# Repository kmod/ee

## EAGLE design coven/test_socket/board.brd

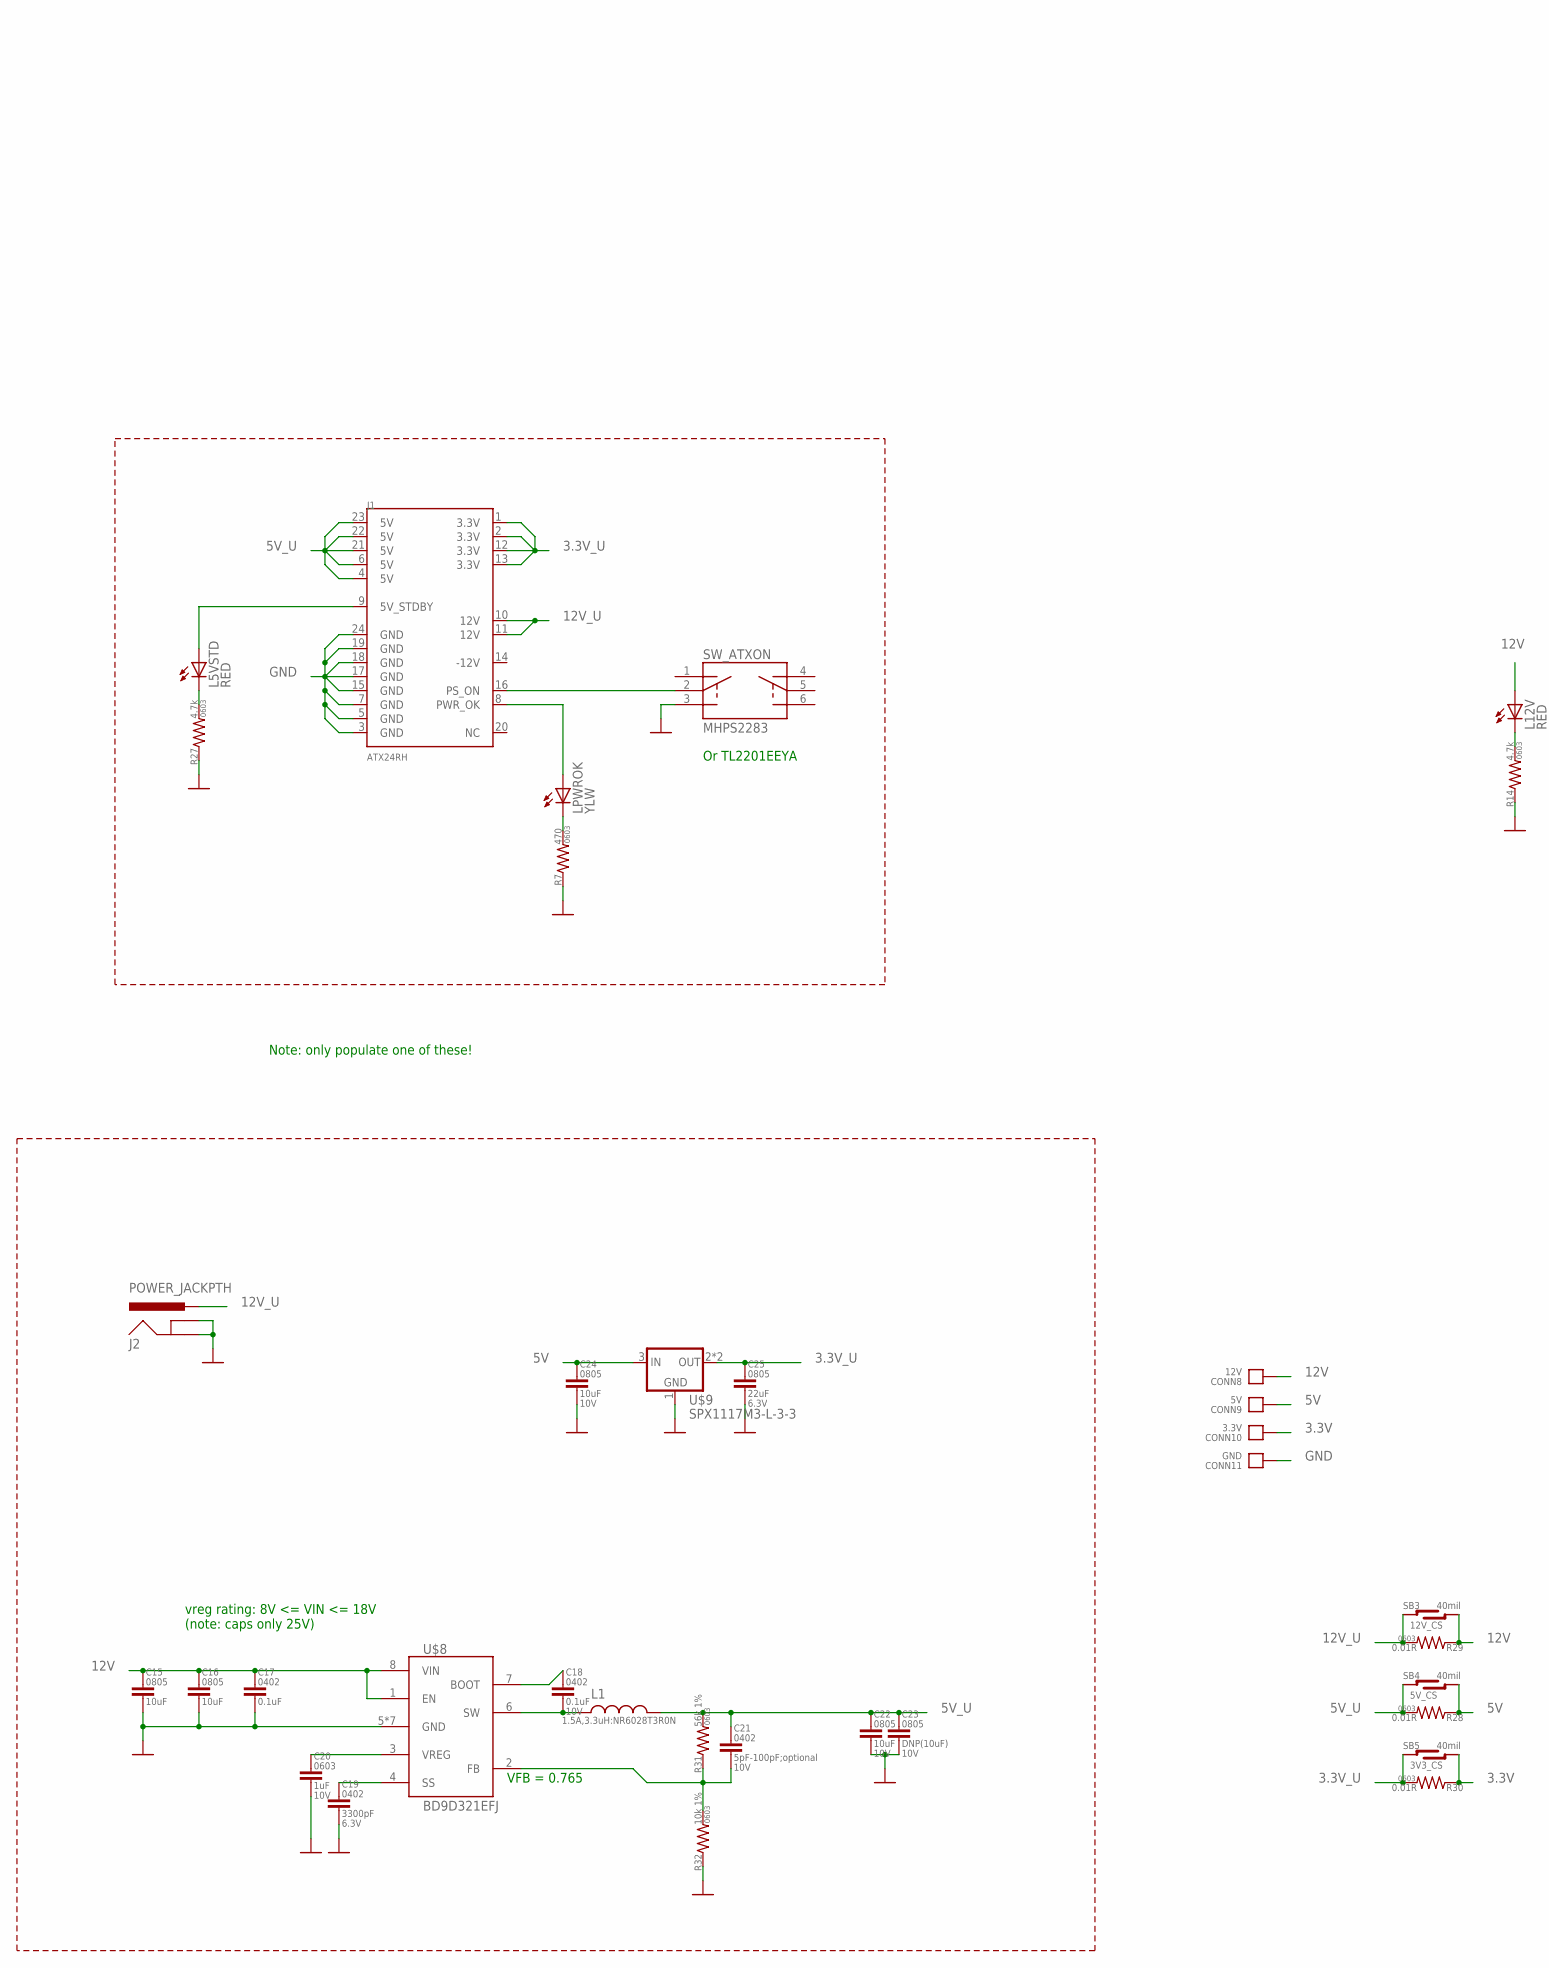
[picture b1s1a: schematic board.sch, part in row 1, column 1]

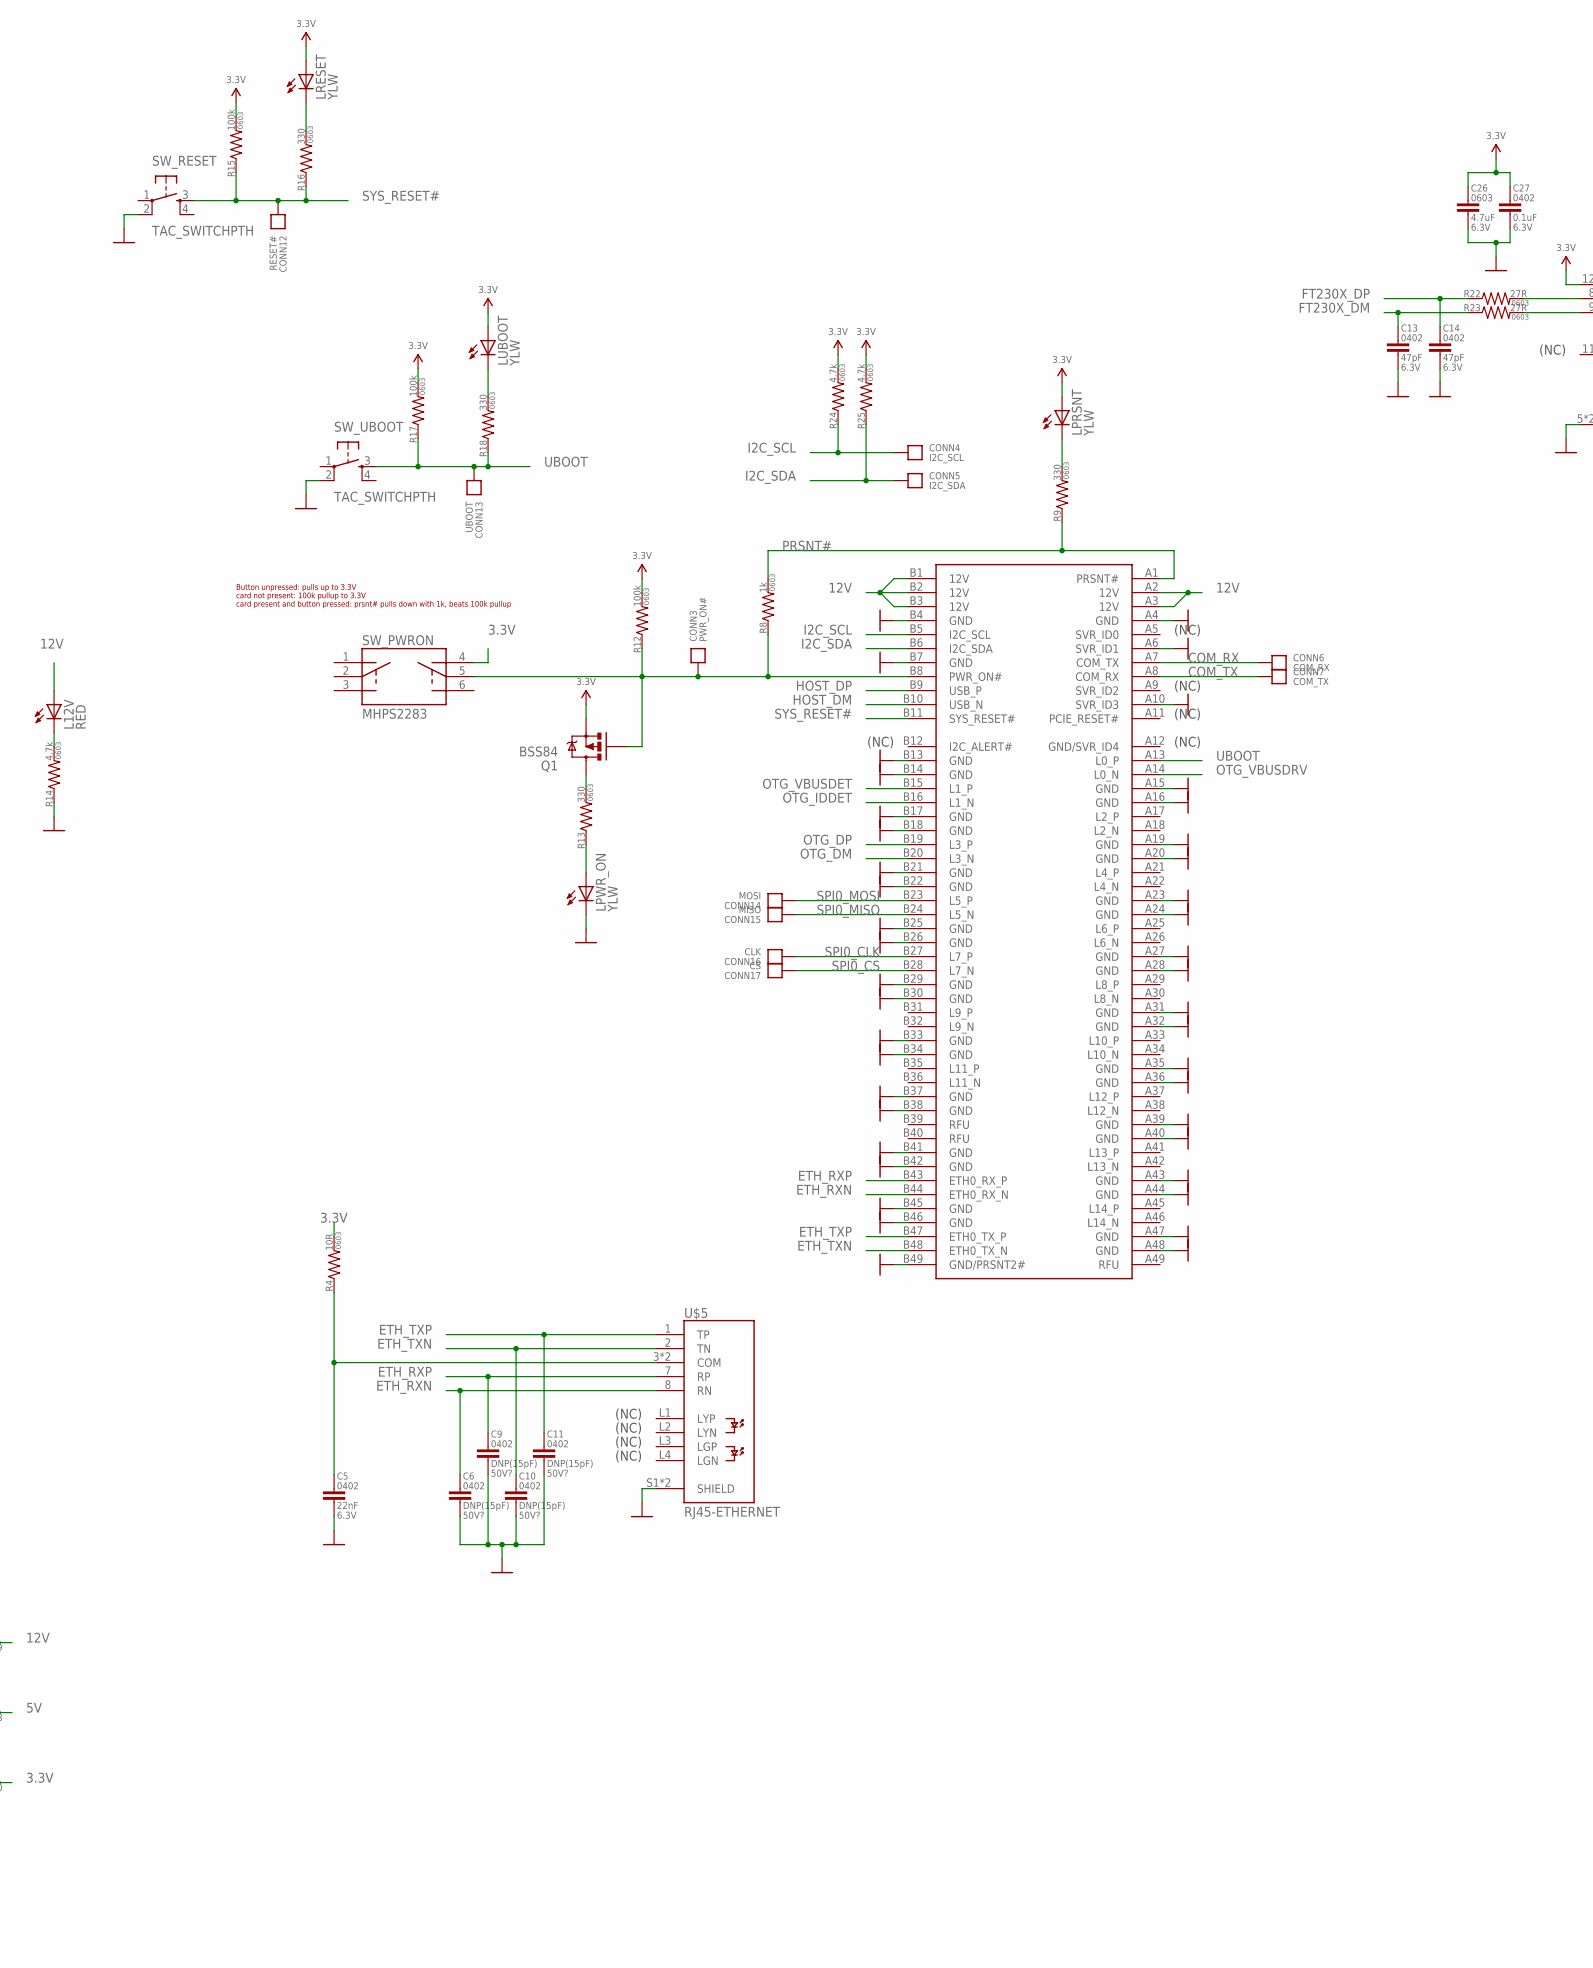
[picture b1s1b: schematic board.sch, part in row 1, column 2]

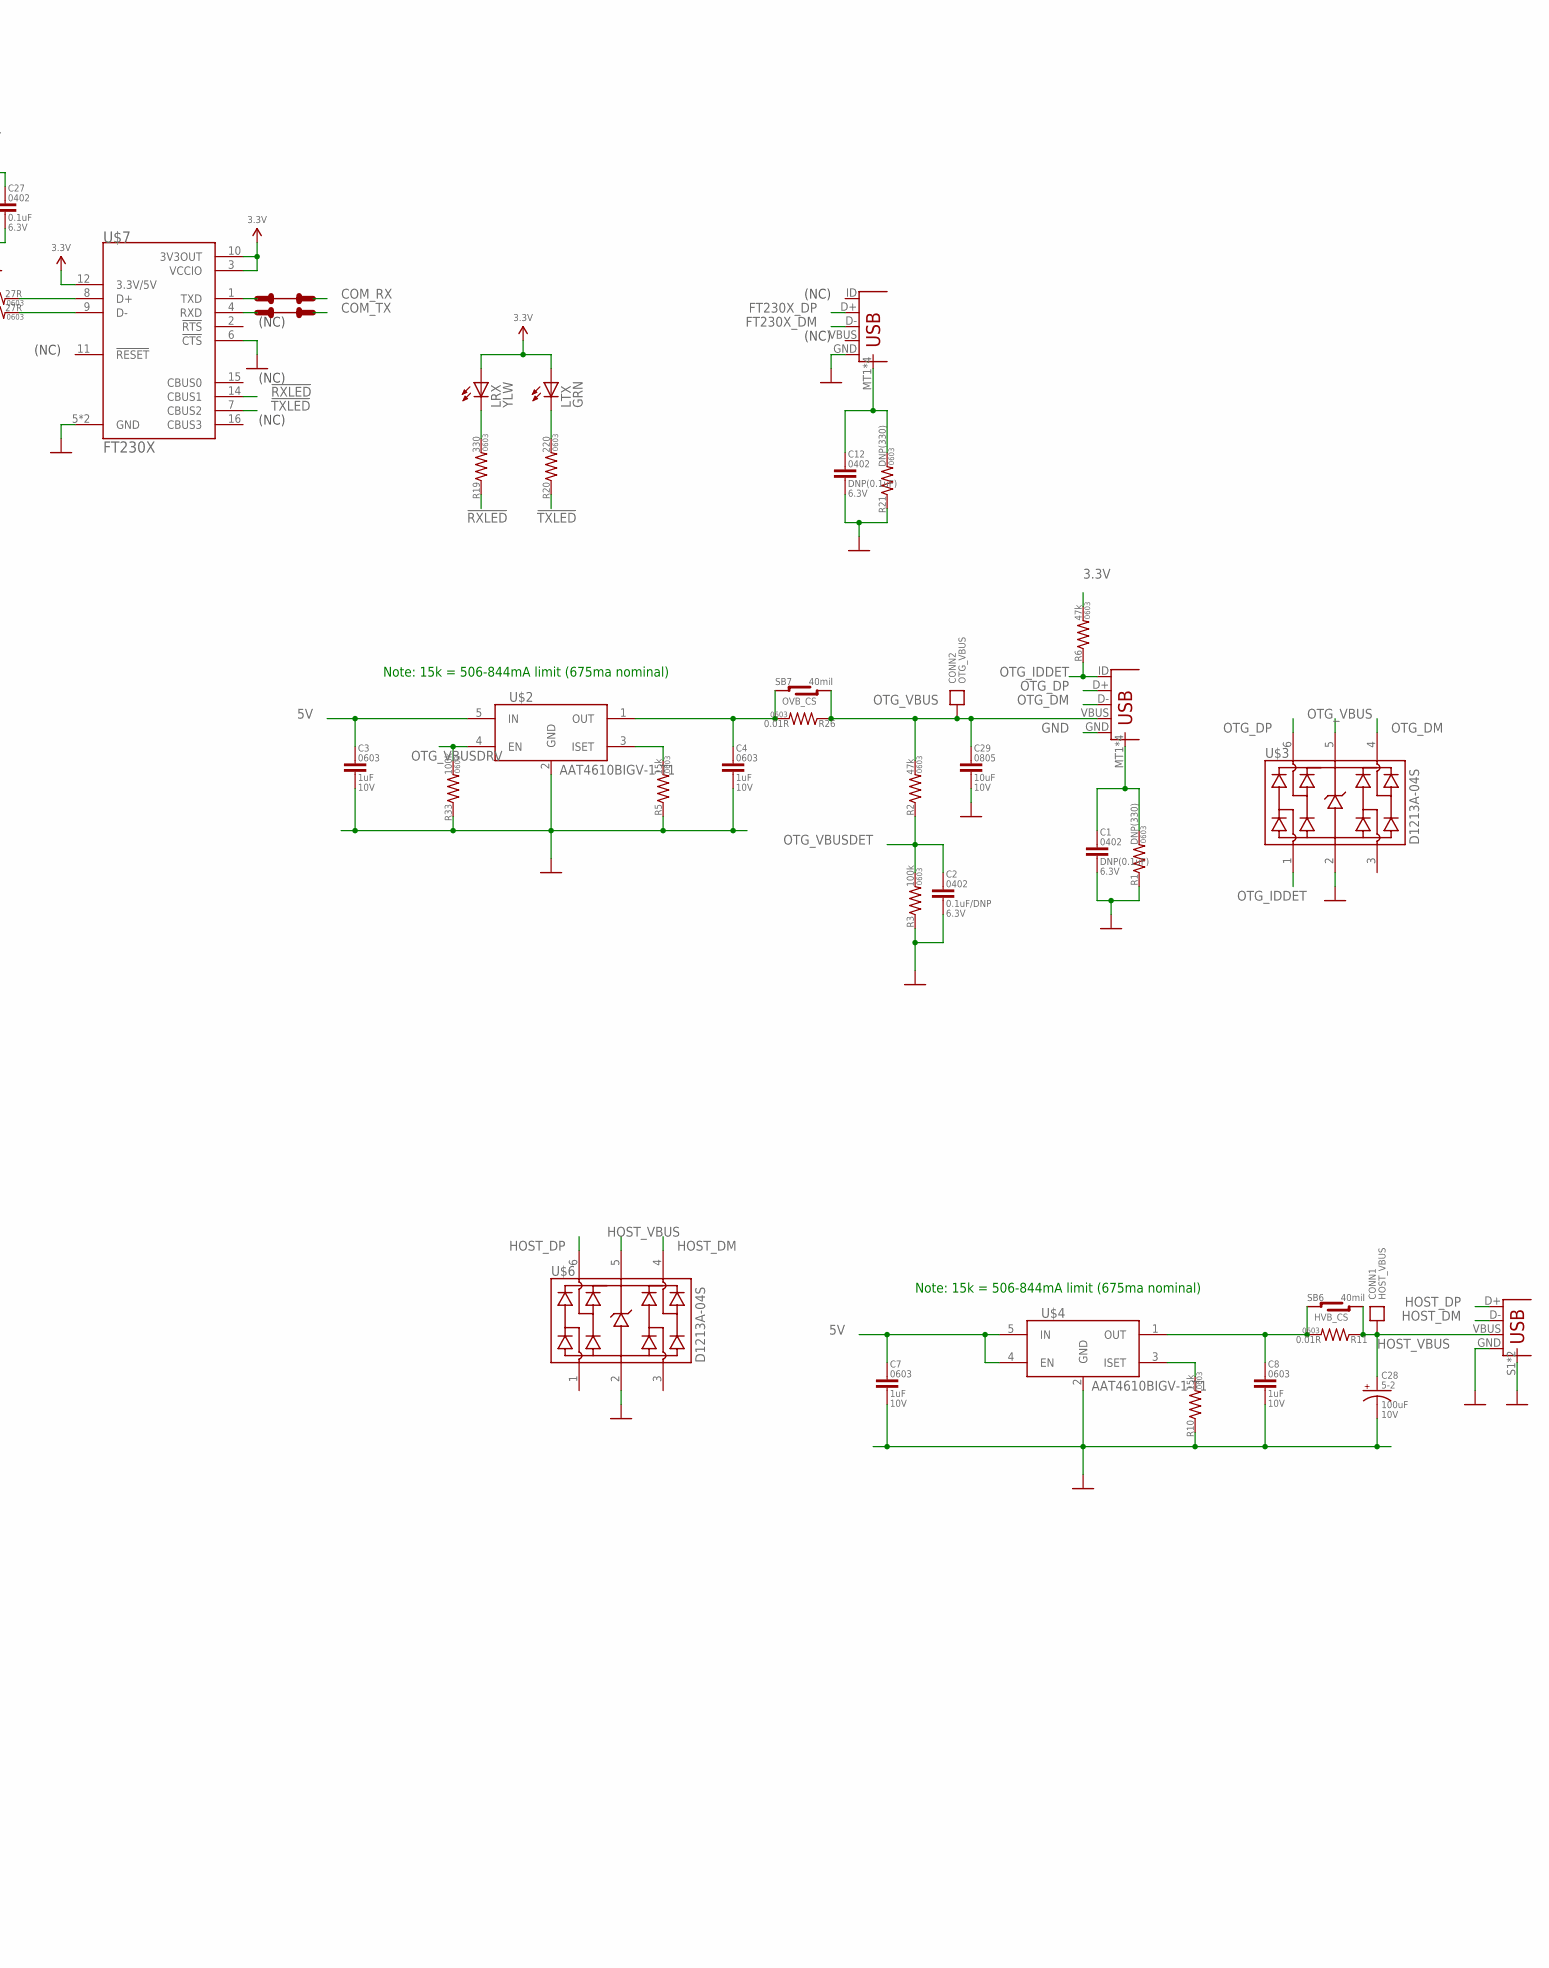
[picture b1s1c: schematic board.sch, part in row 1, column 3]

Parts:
C1, C12: DNP(0.1uF); 0402-CAP
C2: 0.1uF/DNP; 0402-CAP
C3, C4, C7, C8, C20: 1uF; 0603-CAP; VOLTAGE 10V
C5: 22nF; 0402-CAP
C6, C9, C10, C11: DNP(15pF); 0402-CAP; VOLTAGE 50V?
C13, C14: 47pF; 0402-CAP
C15, C16: 10uF; 0805; VOLTAGE 25V
C17: 0.1uF; 0402-CAP; VOLTAGE 25V
C18: 0.1uF; 0402-CAP; VOLTAGE 10V
C19: 3300pF; 0402-CAP
C21: 5pF-100pF;optional; 0402-CAP; VOLTAGE 10V
C22, C24, C29: 10uF; 0805; VOLTAGE 10V
C23: DNP(10uF); 0805; VOLTAGE 10V
C25: 22uF; 0805
C26: 4.7uF; 0603-CAP
C27: 0.1uF; 0402-CAP
C28: 100uF; CAP-5-2; VOLTAGE 10V
CONN1: HOST_VBUS; HOLE_22AWG
CONN2: OTG_VBUS; HOLE_22AWG
CONN3: PWR_ON#; HOLE_22AWG
CONN4: I2C_SCL; HOLE_22AWG
CONN5: I2C_SDA; HOLE_22AWG
CONN6: COM_RX; HOLE_22AWG
CONN7: COM_TX; HOLE_22AWG
CONN8: 12V; HOLE_22AWG
CONN9: 5V; HOLE_22AWG
CONN10: 3.3V; HOLE_22AWG
CONN11: GND; HOLE_22AWG
CONN12: RESET#; HOLE_22AWG
CONN13: UBOOT; HOLE_22AWG
CONN14: MOSI; HOLE_22AWG
CONN15: MISO; HOLE_22AWG
CONN16: CLK; HOLE_22AWG
CONN17: CS; HOLE_22AWG
J1: ATX24RH; ATX24_RIGHT_ANGLE
J2: POWER_JACKPTH; POWER_JACK_PTH
JP1, JP2: USB-IDMICRO; USB-MICRO
JP3: USBA-FEMALE-TH; USB-A-SOCKET-TH
L1: 1.5A,3.3uH:NR6028T3R0N; NR60XX
L5VSTD, L12V: RED; 0603_LED
LPRSNT: YLW; 0603_LED
LPWROK: YLW; 0603_LED
LPWR_ON: YLW; 0603_LED
LRESET: YLW; 0603_LED
LRX: YLW; 0603_LED
LTX: GRN; 0603_LED
LUBOOT: YLW; 0603_LED
Q1: BSS84; SOT23-3
R1, R21: DNP(330); 0603-RES
R2, R6: 47k; 0603-RES
R3, R12, R15, R17, R33: 100k; 0603-RES
R4: 10R; 0603-RES
R5, R10: 15k; 0603-RES
R7: 470; 0603-RES
R8: 1k; 0603-RES
R9, R13, R16, R18, R19: 330; 0603-RES
R11, R26, R28, R29, R30: 0.01R; 0603-RES
R14, R24, R25, R27: 4.7k; 0603-RES
R20: 220; 0603-RES
R22, R23: 27R; 0603-RES
R31: 56k 1%; 0603-RES
R32: 10k 1%; 0603-RES
SB1: RX; TRACE-CUT
SB2: TX; TRACE-CUT
SB3: 12V_CS; SOLDER-BRIDGE-OPEN-LARGE
SB4: 5V_CS; SOLDER-BRIDGE-OPEN-LARGE
SB5: 3V3_CS; SOLDER-BRIDGE-OPEN-LARGE
SB6: HVB_CS; SOLDER-BRIDGE-OPEN-LARGE
SB7: OVB_CS; SOLDER-BRIDGE-OPEN-LARGE
SW_ATXON: MHPS2283; PUSHBUTTON-2.5-5.4
SW_PWRON: MHPS2283; PUSHBUTTON-2.5-5.4
SW_RESET: TAC_SWITCHPTH; TACTILE-PTH
SW_UBOOT: TAC_SWITCHPTH; TACTILE-PTH
U$1: CVN-V1CONN; CVN-V1-CONN
U$2, U$4: AAT4610BIGV-1-T1; SOT23-5
U$3, U$6: D1213A-04S; SOT363
U$5: RJ45-ETHERNET; RJ45
U$7: FT230X; TSSOP16
U$8: BD9D321EFJ; HTSOP8
U$9: SPX1117M3-L-3-3; SOT223

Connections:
3.3V: C26.1, C27.1, CONN10.P, LPRSNT.A, LRESET.A, LRX.A, LTX.A, LUBOOT.A, Q1.2 (S), R4.2, R6.2, R12.2, R15.2, R17.2, R24.2, R25.2, R30.1, SB5.R1, SB5.R2, SW_PWRON.4 (NC1), U$7.3 (VCCIO), U$7.10 (3V3OUT), U$7.12 (3.3V/5V)
3.3V_U: C25.1, J1.1 (3.3V), J1.2 (3.3V), J1.12 (3.3V), J1.13 (3.3V), R30.2, SB5.L1, SB5.L2, U$9.2 (OUT), U$9.4 (OUT)
5V: C3.1, C7.1, C24.1, CONN9.P, R28.1, SB4.R1, SB4.R2, U$2.5 (IN), U$4.4 (EN), U$4.5 (IN), U$9.3 (IN)
5V_U: C21.1, C22.1, C23.1, J1.4 (5V), J1.6 (5V), J1.21 (5V), J1.22 (5V), J1.23 (5V), L1.P$2 (2), R28.2, R31.2, SB4.L1, SB4.L2
12V: C15.1, C16.1, C17.1, CONN8.P, L12V.A, R29.1, SB3.R1, SB3.R2, U$1.A2 (12V), U$1.A3 (12V), U$1.B1 (12V), U$1.B2 (12V), U$1.B3 (12V), U$8.1 (EN), U$8.8 (VIN)
12V_U: J1.10 (12V), J1.11 (12V), J2.PWR, R29.2, SB3.L1, SB3.L2
!RXLED: R19.1, U$7.14 (CBUS1)
!TXLED: R20.1, U$7.7 (CBUS2)
COM_RX: CONN6.P, SB1.R1, U$1.A7 (COM_TX)
COM_TX: CONN7.P, SB2.R1, U$1.A8 (COM_RX)
ETH_RXN: C6.1, U$1.B44 (ETH0_RX_N), U$5.8 (RN)
ETH_RXP: C9.1, U$1.B43 (ETH0_RX_P), U$5.7 (RP)
ETH_TXN: C10.1, U$1.B48 (ETH0_TX_N), U$5.2 (TN)
ETH_TXP: C11.1, U$1.B47 (ETH0_TX_P), U$5.1 (TP)
FT230X_DM: C13.1, JP2.D-, R23.1
FT230X_DP: C14.1, JP2.D+, R22.1
GND: C1.2, C2.2, C3.2, C4.2, C5.2, C6.2, C7.2, C8.2, C9.2, C10.2, C11.2, C12.2, C13.2, C14.2, C15.2, C16.2, C17.2, C19.2, C20.2, C22.2, C23.2, C24.2, C25.2, C26.2, C27.2, C28.2 (-), C29.2, CONN11.P, J1.3 (GND), J1.5 (GND), J1.7 (GND), J1.15 (GND), J1.17 (GND), J1.18 (GND), J1.19 (GND), J1.24 (GND), J2.GND, J2.GNDBREAK, JP1.GND, JP2.GND, JP3.GND, JP3.S1 (SHELL), JP3.S2 (SHELL), LPWR_ON.C, R1.1, R3.1, R5.1, R7.1, R10.1, R14.1, R21.1, R27.1, R32.1, R33.1, SW_ATXON.3 (NO0), SW_RESET.2, SW_UBOOT.2, U$1.A4 (GND), U$1.A6 (SVR_ID1), U$1.A10 (SVR_ID3), U$1.A15 (GND), U$1.A16 (GND), U$1.A19 (GND), U$1.A20 (GND), U$1.A23 (GND), U$1.A24 (GND), U$1.A27 (GND), U$1.A28 (GND), U$1.A31 (GND), U$1.A32 (GND), U$1.A35 (GND), U$1.A36 (GND), U$1.A39 (GND), U$1.A40 (GND), U$1.A43 (GND), U$1.A44 (GND), U$1.A47 (GND), U$1.A48 (GND), U$1.B4 (GND), U$1.B7 (GND), U$1.B13 (GND), U$1.B14 (GND), U$1.B17 (GND), U$1.B18 (GND), U$1.B21 (GND), U$1.B22 (GND), U$1.B25 (GND), U$1.B26 (GND), U$1.B29 (GND), U$1.B30 (GND), U$1.B33 (GND), U$1.B34 (GND), U$1.B37 (GND), U$1.B38 (GND), U$1.B41 (GND), U$1.B42 (GND), U$1.B45 (GND), U$1.B46 (GND), U$1.B49 (GND/PRSNT2#), U$2.2 (GND), U$3.2 (VN), U$4.2 (GND), U$5.S1 (SHIELD), U$5.S2 (SHIELD), U$6.2 (VN), U$7.5 (GND), U$7.6 (!CTS), U$7.13 (GND), U$8.5 (GND), U$8.P$1 (GND), U$8.P$2 (GND), U$8.P$3 (GND), U$8.P$4 (GND), U$8.P$5 (GND), U$8.PAD (GND), U$9.1 (GND)
HOST_DM: JP3.D-, U$1.B10 (USB_N), U$6.4 (CH3)
HOST_DP: JP3.D+, U$1.B9 (USB_P), U$6.6 (CH4)
HOST_VBUS: C28.1 (+), CONN1.P, JP3.VBUS, R11.1, SB6.R1, SB6.R2, U$6.5 (VP)
HOST_VBUS_U: C8.1, R11.2, SB6.L1, SB6.L2, U$4.1 (OUT)
I2C_SCL: CONN4.P, R24.1, U$1.B5 (I2C_SCL)
I2C_SDA: CONN5.P, R25.1, U$1.B6 (I2C_SDA)
unnamed: J1.16 (PS_ON), SW_ATXON.2 (COM0)
unnamed: J1.8 (PWR_OK), LPWROK.A
unnamed: C1.1, JP1.MT1 (SHELL), JP1.MT2 (SHELL), JP1.P$1 (SHELL), JP1.P$2 (SHELL), R1.2
unnamed: C5.1, R4.1, U$5.3 (COM), U$5.6 (COM)
unnamed: R5.2, U$2.3 (ISET)
unnamed: Q1.3 (D), R13.2
unnamed: LPWROK.C, R7.2
unnamed: LRX.C, R19.2
unnamed: LTX.C, R20.2
unnamed: R10.2, U$4.3 (ISET)
unnamed: LPRSNT.C, R9.2
unnamed: LPWR_ON.A, R13.1
unnamed: LRESET.C, R16.2
unnamed: L12V.C, R14.2
unnamed: LUBOOT.C, R18.2
unnamed: R23.2, U$7.9 (D-)
unnamed: C12.1, JP2.MT1 (SHELL), JP2.MT2 (SHELL), JP2.P$1 (SHELL), JP2.P$2 (SHELL), R21.2
unnamed: SB1.L1, U$7.1 (TXD)
unnamed: SB2.L1, U$7.4 (RXD)
unnamed: R22.2, U$7.8 (D+)
unnamed: L5VSTD.C, R27.2
unnamed: J1.9 (5V_STDBY), L5VSTD.A
unnamed: C18.1, U$8.7 (BOOT)
unnamed: C18.2, L1.P$1 (1), U$8.6 (SW)
unnamed: C20.1, U$8.3 (VREG)
unnamed: C19.1, U$8.4 (SS)
unnamed: C21.2, R31.1, R32.2, U$8.2 (FB)
OTG_DM: JP1.D-, U$1.B20 (L3_N), U$3.4 (CH3)
OTG_DP: JP1.D+, U$1.B19 (L3_P), U$3.6 (CH4)
OTG_IDDET: JP1.ID, R6.1, U$1.B16 (L1_N), U$3.1 (CH1)
OTG_VBUS: C29.1, CONN2.P, JP1.VBUS, R2.2, R26.1, SB7.R1, SB7.R2, U$3.5 (VP)
OTG_VBUSDET: C2.1, R2.1, R3.2, U$1.B15 (L1_P)
OTG_VBUSDRV: R33.2, U$1.A14 (L0_N), U$2.4 (EN)
OTG_VBUS_U: C4.1, R26.2, SB7.L1, SB7.L2, U$2.1 (OUT)
PRSNT#: R8.2, R9.1, U$1.A1 (PRSNT#)
PWR_ON#: CONN3.P, Q1.1 (G), R8.1, R12.1, SW_PWRON.5 (COM1), U$1.B8 (PWR_ON#)
SPI0_CLK: CONN16.P, U$1.B27 (L7_P)
SPI0_CS: CONN17.P, U$1.B28 (L7_N)
SPI0_MISO: CONN15.P, U$1.B24 (L5_N)
SPI0_MOSI: CONN14.P, U$1.B23 (L5_P)
SYS_RESET#: CONN12.P, R15.1, R16.1, SW_RESET.3, U$1.B11 (SYS_RESET#)
UBOOT: CONN13.P, R17.1, R18.1, SW_UBOOT.3, U$1.A13 (L0_P)

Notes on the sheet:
(NC)
Note: 15k = 506-844mA limit (675ma nominal)
Or TL2201EEYA
VFB = 0.765
vreg rating: 8V <= VIN <= 18V (note: caps only 25V)
Note: only populate one of these!
Button unpressed: pulls up to 3.3V card not present: 100k pullup to 3.3V card present and button pressed: prsnt# pulls down with 1k, beats 100k pullup

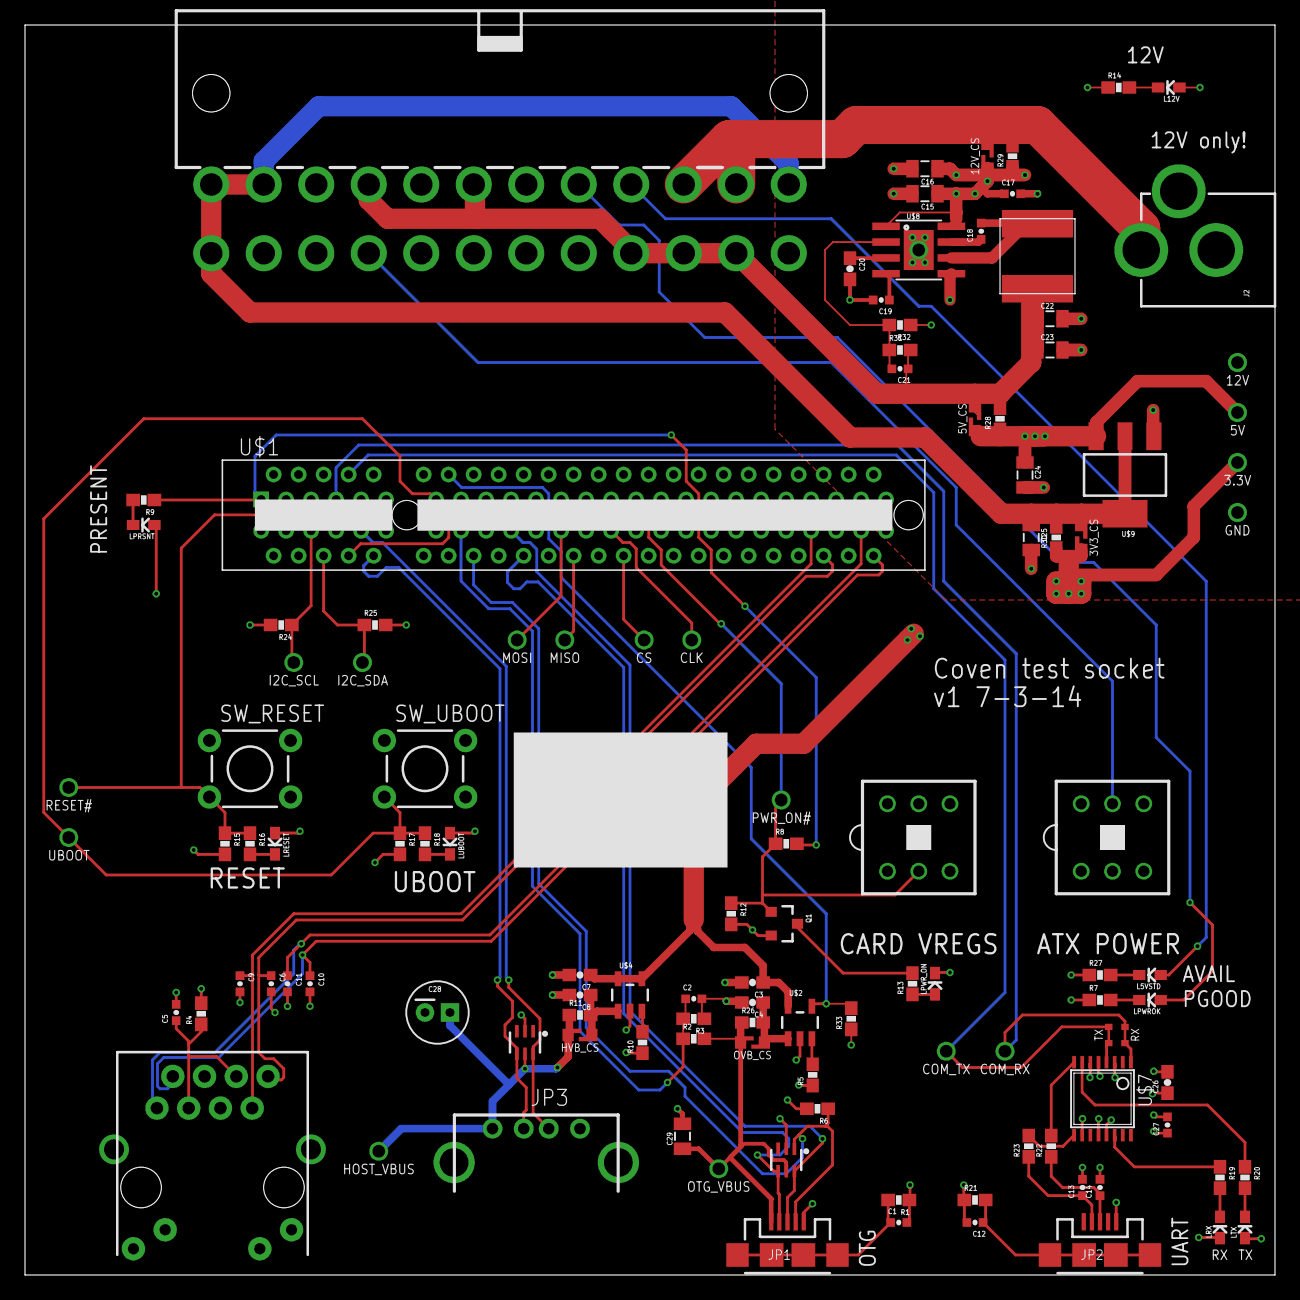
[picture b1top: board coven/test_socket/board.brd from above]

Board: 4 copper layers, 100.0 x 100.0 mm, 115 parts (0 on the bottom side), 65 nets.

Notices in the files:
parts and their libraries:
SparkFun-DiscreteSemi: Licensing: CC v3.0 Share-Alike You are welcome to use this library for commercial purposes.
SparkFun-Connectors: Licensing: Creative Commons ShareAlike 4.0 International - https://creativecommons.org/licenses/by-sa/4.0
SparkFun-Aesthetics: Released under the Creative Commons
